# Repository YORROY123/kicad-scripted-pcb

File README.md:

# kicad-scripted-pcb

**[繁體中文](README.zh-TW.md)**

Three KiCad 10 boards designed entirely as code: Python scripts produce the schematic, the PCB
placement, the routing (via [freerouting](https://github.com/freerouting/freerouting)) and the
copper pours, and each board rebuilds from scratch with one command. The KiCad GUI is never opened.

The point is **verification**. Every build runs several independent checks, because each one is
blind to errors the others catch. Some of those errors turned up while these boards were being
built and are listed below.

| | Board | Result |
|---|---|---|
|  | **usbc-ldo**: USB-C 5 V → 3.3 V LDO → LED. 40 × 24 mm, 2 layers. Includes an ngspice power-path simulation. | ERC 0, DRC 0, schematic parity |
|  | **esp32c3**: ESP32-C3 minimal board with native USB, LP38693 LDO, RESET/BOOT, LEDs and an 8-pin header. 32 × 49 mm. | ERC 0, DRC 0, schematic parity, pin-by-pin netlist check |
|  | **relay8**: ESP32-C3 + ULN2803 driving 8 mains relays from **one mains cable**: on-board HLK-10M05 AC-DC (100–240 VAC), T8A fuse, varistor, L/N bus traces, per-channel NO · N · NC terminals, isolation slots and custom mains clearance rules. 232 × 110 mm. **Not safety-certified.** | ERC 0, DRC errors 0 (40 silkscreen-clipped-by-slot/edge warnings listed), schematic parity |

Each ESP32 board has a `FIRMWARE.md` with the pin map, flashing steps, a first program, and, for
relay8, the mains wiring.

## Pipeline

```
gen/board.py ──► .kicad_sch ──► ERC ──► netlist ──► netlist check (vs expected_nets.json)
                                                     │
                                                     ▼
                                     design review (lib/review.py, datasheet rules)
                                                     │
gen/pcb.py ◄─────────────────────────────────────────┘   place footprints, board outline,
   │                                                     net classes, placement self-check
   ▼
.kicad_pcb ──► Specctra DSN ──► freerouting ──► SES ──► import + GND pour ──► DRC (+ schematic parity)
                                                                                   │
                     lcsc.json ──► lib/lcsc.py (online, run by hand) ──► lcsc-check.json
                                                                                   │
                                                       lib/fab.py ◄────────────────┘
                                     Gerber + drill zip, JLCPCB BOM / CPL, hand-solder list
```

Every step stops the build on failure; nothing is passed downstream with a known error.

`kicad-cli` has no "update PCB from schematic" command, so `lib/pcbgen.py` builds the board from
the exported netlist with pcbnew.

## What each check catches, and what it missed

| Check | Catches | Missed here (caught by something else) |
|---|---|---|
| `schgen.crossing_pins()` / `overlapping_wires()` | a wire running across a pin (silent short), two nets merged by overlapping wires | — |
| KiCad ERC | unconnected pins, undriven power | **LED wired backwards** (two passive pins, ERC is fine with it). Found by reading the netlist while building the PCB. |
| `check_netlist.py` vs `expected_nets.json` | wrong pin→net, single-pin nets | ERC ignores "global label appears only once" **by default**, so a label typo creates an isolated net with no ERC error. Proven with a deliberate typo (mutation test). |
| placement self-check | pad nets vs netlist, footprints off-board, courtyard overlap | Uses real courtyard polygons. The ESP32 module's courtyard is T-shaped, and bounding boxes reject legal positions. |
| DRC + `--schematic-parity` | clearance, track width, edge clearance, schematic vs PCB | — |
| custom DRC rules (`relay8.kicad_dru`) | mains ↔ low voltage ≥ 3.0 mm, mains ↔ mains ≥ 2.4 mm | Creepage around the slots is not checked by DRC. Needs a human. |
| ngspice simulation (`usbc-ldo/sim`) | design margins | The first board's 1.1 V-dropout LDO falls out of regulation at USB's 4.40 V minimum, and its input capacitance injects ~124 µC on hot-plug (USB 2.0 limit: 50 µC). All three boards now use LP38693 (12 V input rating): `esp32c3/sim` showed that with only 1 µF on VBUS, hot-plug cable ringing reaches 7.7–8.6 V, above the 6.5 V rating of the AP2112K the ESP32 boards first used. |
| `lib/review.py` design review (datasheet rules on the netlist) | wrong *intent*: diode/TVS polarity, LED current from the real Vf range, decoupling and rail ranges per datasheet, USB-C CC pull-downs, ESP32-C3 EN RC / strapping pins / GPIO18-19, relay flyback path and pickup voltage, capacitor voltage and polarity, per-supply current budget, LDO junction temperature, USB VBUS capacitance | **usbc-ldo's SMAJ5.0A TVS was wired backwards**: anode on +5 V, cathode on GND, a short the moment USB is plugged in. KiCad's symbol names the cathode pin "A1". ERC, DRC, the netlist check and the SPICE model (which had it the right way round) all passed. It also found a blue LED on a 3.3 V GPIO (Vf up to 3.6 V) and green power LEDs at ~0.45 mA. `lib/review_test.py` breaks the real netlists 20 ways and expects each rule to fire. |
| `lib/lcsc.py` + `lib/fab.py` | LCSC part number vs model, stock, package size, R/C value, LED colour; symbol default footprint vs assigned footprint; drill count; BOM/CPL/board refdes | All three boards used the USBLC6-2**P6** symbol (SOT-666) on a SOT-23-6 footprint: same pinout, so nothing else noticed, but a BOM by value buys parts that do not fit. The SMAJ5.0A part number first chosen had zero stock. |

## Things that cost time (so they don't cost yours)

- **freerouting-cli 2.5.0 crashes** on KiCad 10 DSN files ([freerouting#957](https://github.com/freerouting/freerouting/issues/957)). Use the jar, which needs Java 25.
- freerouting's **automatic neck-down** narrows tracks to 0.125 mm beside 0402 pads, below JLCPCB's 0.127 mm minimum. Use `--router.automatic_neckdown=false --router.neck_width_um=150`.
- The DSN carries no copper-to-edge rule. Pass `--router.copper_to_edge_clearance_um`. That setting **does not cover internal slots**, so put keepouts around slots.
- Net classes live in `.kicad_pro`, not `.kicad_pcb`. Save with `pcbnew.SaveBoard()`, which writes both.
- `board.Remove(zone)` from Python can raise `'SwigPyObject' has no attribute 'thisown'` or crash pcbnew (0xC0000005). Use `board.Delete()`.
- freerouting reports pin-to-pin "violations" inside fine-pitch footprints where KiCad's DRC is clean. The cause is KiCad's DSN exporter inflating **every** edge of a rounded-rect pad (`specctra_export.cpp`) by the arc-approximation margin.
- Windows PowerShell 5.1 reads BOM-less UTF-8 scripts as ANSI. The build scripts here are ASCII-only for that reason.

## Requirements

- Windows (the build scripts are PowerShell; the Python parts are cross-platform)
- [KiCad 10](https://www.kicad.org/) (uses its bundled Python for pcbnew, and its ngspice). Set `KICAD_BIN` / `KICAD_SHARE` if it is not in the default location.
- Python 3.10+ on PATH for schematic generation and the design review (standard library only). The simulations and the field solver need `numpy`, `scipy` and `matplotlib`.
- Network access only for `lib/lcsc.py` (JLCPCB parts API). The build itself runs offline.
- freerouting 2.5.0 jar + a Java 25 runtime. Run `tools\setup-tools.ps1` once; it downloads both into `tools\` with pinned SHA-256 checks.

## Quick start

```powershell
powershell -ExecutionPolicy Bypass -File tools\setup-tools.ps1
powershell -ExecutionPolicy Bypass -File boards\esp32c3\build.ps1
python lib\review_test.py          # design-review mutation tests; needs the boards built once
```

The build ends with `boards/<b>/fab/`:

| File | Use |
|---|---|
| `<b>-gerber.zip` | upload to JLCPCB as the PCB |
| `<b>-bom.csv`, `<b>-cpl.csv` | upload for SMT assembly (parts LCSC can supply) |
| `hand-solder.csv` | parts LCSC cannot supply (relay8: mains terminals, fuse holders) |
| `rotation-review.csv` | every part's CPL rotation and where it came from. None is hardware-verified: compare each part in JLCPCB's placement preview |

Also written to `boards/<b>/`: `review.txt` (design review, including the inferred net voltages) and
`lcsc-check.json` (part numbers as checked against JLCPCB, with stock and attributes).

## Layout

```
lib/schgen.py, ksym.py, netlabel.py   schematic writer (symbols flattened from the KiCad library)
lib/check_netlist.py                  netlist vs expected_nets.json
lib/review.py, review_test.py         design review rules + mutation tests
lib/pcbgen.py, route.py               PCB builder (BoardSpec), freerouting round trip, GND pour
lib/lcsc.py, fab.py, jlc_rotations.json   part-number check, fabrication outputs
lib/field2d.py, field2d_check.py      2-D field solver for trace impedance + validation
boards/<b>/gen/board.py   the circuit (pin -> net table)
boards/<b>/gen/pcb.py     placement (BoardSpec)
boards/<b>/lcsc.json      hand-written LCSC part numbers ("value|footprint" -> part)
boards/<b>/review-waivers.json   accepted review findings, each with a reason
boards/<b>/build.ps1      one-command build
boards/<b>/sim/           ngspice and field-solver studies
tools/      setup-tools.ps1 (downloads are git-ignored)
```

Want to add a board or a review rule? See [CONTRIBUTING.md](CONTRIBUTING.md).

Code comments are in Chinese. The boards were built while comparing AI-assisted workflows in
KiCad and EasyEDA Pro.

## Limits

These are two-layer boards with modules and simple power. There is no controlled-impedance routing,
no length matching, no BGA and no SI/PI analysis; freerouting does none of these (`lib/field2d.py`
can tell you whether a trace needs it). The fabrication files are complete enough to order, but
nobody has built these boards yet: CPL rotations are unverified and the design review is a set of
rules, not an engineer. Have a person review before ordering. This applies above all to
**relay8**, which switches mains voltage.

## License

MIT. freerouting (GPL-3.0) and the Temurin JRE (GPL-2.0 with Classpath Exception) are downloaded at
setup time and are not part of this repository.

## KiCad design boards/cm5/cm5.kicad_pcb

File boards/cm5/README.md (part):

# CM5 carrier(進行中)

Raspberry Pi Compute Module 5(含 eMMC)的通用載板,目標是 JLCPCB 能直接 PCBA,CM5 自己插上。

原理圖已完成。PCB 進行中:擺件完成,佈線第一、二階段(兩級降壓的鋪銅與過孔、閘極驅動)完成,第三階段(差分線)全部手佈完成,其餘還沒佈線(交給 freerouting)。3D 預覽在 [`concept/`](concept/README.md)。

## PCB(進行中)

`gen/pcb.py` 讀網表擺出 `cm5.kicad_pcb`;座標與自動擺件在 `gen/placement.py`,3D 預覽也用同一份。
電源級的外層鋪銅、過孔與手佈走線在 `gen/power_stage.py`(見「電源級」「閘極驅動」兩節)。
差分線在 `gen/diff_pairs.py`(見「差分線」)。

- 170 × 120 mm、4 層。固定孔:板子 M3 ×4(H1–H4),CM5 模組 M2.5 ×4(H5–H8)。
- 網路類別(線寬由電流算,見下一節「外層電源走線」):`HV54`(+54V、VIN_RAW;1.4 mm、間距 0.25 mm)、
  `PoE`(POE*;0.5 mm、0.25 mm)、`Switch`(SW、SW3;主路徑是鋪銅)、`Rail5`(+5V;2.7 mm)、`Rail3`(+3V3;1.1 mm)、
  `USB5V`(USB-A / HDMI / USB-C 的 VBUS;0.75 mm)、`Power`(GND 與其他小電源;0.5 mm)。
  54 V 間距取 IPC-2221 表 6-1 的 B4(外層有防焊,51–100 V 0.13 mm)再留餘量;B2(無塗層)的 0.6 mm
  零件本身做不到(RJ45 腳間 0.53、IP804AR 0.25)。
- `cm5.kicad_dru`:同一顆零件的焊盤之間最小 0.1 mm(FSUSB42 MSOP-10 焊盤間只有 0.15 mm),
  走線與過孔仍照網路類別。拿掉這個檔,DRC 會報 FSUSB42 的 8 個間距錯誤。
- 自檢(`lib/pcbgen.py`):焊盤逐腳對網表、courtyard 真實多邊形不重疊、不出板(板邊接頭只查焊盤)。
  `build.ps1` 與 CI 再跑 DRC + 原理圖一致性,除了未連接以外不能有錯誤。
- SW51(FLASH/RUN 滑動開關):撥桿在封裝局部 +y,所以 0°;固定腳到 y=1.83,銅到板邊要 ≥0.5 mm,
  本體退到板邊內 0.75 mm,撥桿伸出約 0.8 mm。外殼開孔時要確認撥得到。

### 差分阻抗(`sim/diff_impedance.py`,結果 `sim/diff_impedance.txt`)

目標照 CM5 規格書 §2.2–2.5:PCIe、USB 3.0、USB 2.0 都是 **90 Ω**,HDMI 與乙太網路 **100 Ω**
(先前這裡寫 PCIe 85 Ω 是錯的)。疊構 JLC04161H-3313(jlcpcb.com/impedance):L1 銅 0.035 mm、
3313 預浸料 0.0994 mm、εr 4.1,差分線走 L1、參考 L2 整片地(L4 對 L3 疊構相同,但 L3 是電源平面,只用來短暫下穿)。`lib/field2d.py` 外推到格距 → 0:

| 用途 | 目標 | 線寬 | 間距 | 算出 |
|---|---|---|---|---|
| PCIe / USB3 / USB2 | 90 Ω | 0.165 mm | 0.15 mm | 90.5 Ω |
| 同上(較緊) | 90 Ω | 0.155 mm | 0.13 mm | 91.0 Ω |
| HDMI / Ethernet | 100 Ω | 0.145 mm | 0.20 mm | 100.2 Ω |
| 同上(較緊) | 100 Ω | 0.130 mm | 0.15 mm | 101.0 Ω |

- 同層鋪銅離差分線 ≥ 0.25 mm 時,阻抗只低 0.4%;0.15 mm 會低 1.5%。
- 防焊漆沒建模(實際再低約 1–3 Ω),所以結果故意落在目標上方。下單前要用 JLC 自己的計算器
  (有建模防焊與梯形線)對一次,並選阻抗控制。
- 換層:L1 ↔ L4 的參考面從 L2(地)換成 L3(電源),旁邊放地過孔接不到 L3,沒有用;要的是 GND–電源的
  縫合電容(見「差分線」待辦)。L4 段不能跨 L3 的 +5V / +3V3 分界。

### 外層電源走線(`gen/pcb.py` 的 `CURRENTS`)

IPC-2221 §6.2 外層公式,外層 1 oz(0.035 mm)、溫升 10 °C。電流取「保護動作前能一直流的電流」:
限流開關用限流**上限**,不是額定。網路類別的線寬比算出的窄,`gen/pcb.py` 就刪掉板檔、回傳失敗。

| 網 | 電流 | 依據 | 需要 | 類別線寬 |
|---|---|---|---|---|
| VIN_RAW、+54V | 3.0 A | 120 W ÷ UVLO 40 V | 1.37 mm | 1.4 mm |
| POE0/1_P、_N | 0.92 A | IP804AR 限流上限(保險絲 1.5 A 只在故障時斷) | 0.27 mm | 0.5 mm |

+5V(→ U62/U63/U70、CM5)與 +3V3(→ M.2)的外層大電流路徑改由「外層供電支線」的鋪銅檢查,
類別線寬降回焊盤放得下的寬度(+5V 0.4、+3V3 0.25),見下一節。
| USBA0/1_VBUS | 1.9 A | AP2171W 限流上限 | 0.73 mm | 0.75 mm |
| HDMI_5V | 1.05 A | TPS2051C 限流上限 | 0.32 mm | 0.75 mm |

- 開關節點與降壓器輸出到內層平面的過孔見下一節「電源級」。
- ⚠ +5V 預算:LM5146 設計 12 A。額定負載 CM5 5 A + 40-pin 1 A + 風扇 0.5 A + USB-A 2 × 1 A + HDMI 0.5 A
  + TPS568230 輸入約 3.0 A(3.3 V × 4 A ÷ 90% ÷ 4.87 V)≈ 12.0 A,剛好到頂。所有限流開關都頂到上限時
  約 14.4 A,會先碰到 LM5146 的限流。要不要降 USB-A 的限流檔或改 12 A 以上的降壓器,佈線前決定。
- `gen/board.py` 的 TPS2051C 註解原本寫限流 0.5–0.9 A,規格書 §6.7(−40–125 °C)是 0.65–1.05 A,已改。

### 外層供電支線(`gen/feeds.py`)與平面扇出(`lib/fanout.py`)

網路類別的線寬整條網共用。+5V 原本 2.7 mm、+3V3 1.1 mm 是照最大的支路算的,結果 LAN7800 / USB2514B
0.25 mm 寬、0.5 mm 腳距的 QFN 腳也要接 1.1 mm 的線,freerouting 扇不出去。現在大電流路徑用固定鋪銅畫死:

| 支線 | 電流 | 做法 | 過孔(每個 0.71 A) |
|---|---|---|---|
| In2 +5V → U62、U63、U70 | 4.85 A | 開關擺在 In2 的 +3V3 區:CM5 模組底邊過孔陣列 → B.Cu 主幹 x 89.5–93.6(避開 USBA0 下穿)→ y 91.3–95.6 橫向 → 每顆 5 腳旁一小塊 F.Cu | 12 / 3 / 3 / 2 |
| In2 +5V → CM5 J1 77–87 | 5 A | 腳下方 F.Cu + 5×2 過孔 | 10 |
| In2 +3V3 → M.2 3V3 腳 | 2.5 A | 右排三組腳外側(卡底下)各一塊 F.Cu | 2 / 3 / 2 |

自檢:載流截面(B.Cu 主幹 3.70 mm ≥ 2.65)、過孔數、F.Cu 小鋪銅的過孔也要落在 B.Cu 主幹上、
每支目標腳最後都接到同網的 In2 平面。突變:U62 過孔 3 → 2、M.2 2/4 腳的鋪銅右移離開焊盤,都會失敗。

平面網路(GND → In1、+3V3 / +5V → In2)的 SMD 焊盤由 `lib/fanout.py` 先打好過孔 + 短線(鎖定):
過孔要落在該網平面的銅上、與異網銅保持兩邊類別較大的間距、孔距 0.25、不進其他零件 courtyard;
短線不比焊盤窄邊寬(CM5 連接器 0.2 mm 焊盤用 0.25 的線離隔壁腳只剩 0.175)。QFN 散熱焊盤
(U40、U41、U50、U61)焊盤內 3×3 過孔。目前 302 個過孔,找不到位置 9 個(C210 / C213 / C230 那裡
In2 是 +3V3 區,沒有 +5V 平面可接,由佈線接到供電支線)。DRC 0。

### 內層電源平面(`gen/pcb.py` 的 `PLANES` / `CORRIDORS`)

- L2(In1.Cu)整片 GND,當 L1 差分線的參考面。
- L3(In2.Cu)分兩塊、中間留 0.5 mm:**+5V** 在右上(x ≥ 60、y ≤ 72),L10 降壓輸出 → CM5、40-pin、風扇;
  **+3V3** 是 L 形(下緣 y ≥ 72 + 左緣 x ≤ 60),L20 降壓輸出 → Hub、LAN7800 ×2 → 往上到 M.2。
- 自檢:每條載流走廊要整塊落在該網的平面裡,而且寬度 ≥ IPC-2221 §6.2 內層公式算出的寬度
  (JLC 內層銅 0.0152 mm、溫升 10 °C;對平面很保守)。不過就刪掉板檔、回傳失敗。

| 網 | 電流 | 走廊寬 | IPC-2221 需要 |
|---|---|---|---|
| +5V(L10 → CM5、40-pin、風扇) | 6.5 A | 71.5 mm | 23.8 mm |
| +3V3(L20 → Hub、LAN7800) | 4.0 A | 47.5 mm | 12.2 mm |
| +3V3(左緣 → M.2) | 2.5 A | 59.5 mm | 6.4 mm |

電流:CM5 5 V 最多 5 A(規格書 §1);M.2 3.3 V 2.5 A(M.2 規範上限);LAN7800 ×2 0.592 A;
40-pin 1 A、風扇 0.5 A、其他 3.3 V 0.3 A 是估計。注意 IPC-2221 這個寬度是 0.5 oz 內層的值:
若整顆降壓器 12 A 都走平面,需要約 55 mm,現在的佈局給得起,但 USB/HDMI 的 5 V 不走平面。
突變:+5V 平面下緣縮到 y = 50 → 走廊落在平面外;+5V 電流改 30 A → 寬度不足,兩者都會失敗。
平面只刪小於 3 mm² 的孤島(`PLANE_MIN_ISLAND_MM2`):40-pin 排針腳之間約 2.2 mm² 的碎銅、過孔陣列之間
< 0.5 mm² 的碎銅都沒接任何東西,以前留著,DRC 報 22 個 isolated_copper 警告;現在 0 個。
還沒接到焊盤的整塊平面不刪。

### 電源級(佈線第一階段;`gen/power_stage.py`)

功率件改成手擺(`gen/placement.py` 的 `PLACE`),照 LM5146 規格書 SNVSBV0A §11.1 與 TPS568230 SLVSEY5C §10.1
(兩份都在 TI 官網);小件仍自動擺,但避開鋪銅與過孔(`power_stage.keepouts()`)。

- **LM5146 → +5V**:Q10 轉 180、Q11 不轉,上下疊。開關節點(Q10 源極、Q11 汲極 → L10)在右側一直線;
  熱迴路(輸入電容 → Q10 汲極 … Q11 源極 → 電容)在左側,C11/C13/C16 的 + 端貼 Q10 汲極、− 端貼 Q11 源極,
  地過孔靠 Q11 源極(§11.1.5)。U10 轉 270,閘極驅動腳朝下正對 Q10;VCC、自舉電容(C20、C21)在 U10 與 Q10 之間。
  54 V 輸入 J20 移到右上,F1 → C10 → 一條 2.1 mm 的 +54V 鋪銅帶往下接輸入電容。
- **TPS568230 → +3V3**:U20 轉 180,VIN 朝右接 C45、SW(19/20 腳)朝下接 L20。整級跨在 In2 分界上:
  輸入取 +5V 平面(5 個過孔),L20 的 2 腳在 +3V3 平面上(8 個過孔)。
- 13 塊 F.Cu 鋪銅都有名字、優先序 1(蓋過之後的整面 GND);80 個過孔鎖定。`lib/route.py` 重新匯入佈線時
  留下它們(`lib/route_test.py`),匯出的 DSN 裡鋪銅是 `plane`、過孔是 `(type fix)`,freerouting 不會動。
- 自檢(`gen/pcb.py` 的 `add_power_stage`,不過就刪掉板檔):每塊鋪銅填得出來、每個過孔在自己網的銅上、
  載流截面整塊有銅、過孔數夠:

| 截面 / 過孔 | 電流 | 寬 | IPC-2221 外層 | 判斷 |
|---|---|---|---|---|
| +54V 帶子(F1 / C10 → 輸入電容) | 3.0 A | 1.7 mm | 1.37 mm | 寬度夠 |
| SW:Q11 汲極 → L10(長 2.35 mm) | 12 A | 4.5 mm | 9.25 mm | 短頸,I²R 37 mW |
| SW3:U20 腳 → L20(長 0.9 mm) | 8 A | 0.85 mm | 5.29 mm | 短頸,I²R 33 mW;受限於 IC 腳寬 |
| +5V:L10 2 腳 → 第一排過孔(長 0.45 mm) | 12 A | 6.3 mm | 9.25 mm | 短頸,I²R 5 mW |
| +3V3:L20 2 腳 → 過孔與輸出電容(長 3.6 mm) | 4.0 A | 2.9 mm | 2.03 mm | 寬度夠 |
| 過孔 L10 → In2 +5V | 12 A | 27 個 | 至少 17 | |
| 過孔 In2 +5V → U20 | 3.0 A | 5 個 | 至少 5 | |
| 過孔 L20 → In2 +3V3 | 4.0 A | 8 個 | 至少 6 | |

  IPC-2221 的寬度是長走線的溫升;開關節點 TI 要求面積越小越好(§11.1.4,它是 EMI 來源),所以 ≤ 3 mm 的
  短頸改算 I²R(銅 1.72e-5 Ω·mm),上限 0.1 W(MOSFET 本身約 1 W 量級)。截面取兩端焊盤之間整段窄處,
  長度照實(只切一薄片的話,任何電流都會被當成短頸放過)。
  突變:拿掉 12 個 +5V 過孔、SW 鋪銅縮窄、過孔移出銅、+3V3 電流改 9 A,四種都會失敗。
- 過孔數改了:以前寫 L10 → +5V 平面 6.5 A、10 個,只算了 CM5、40-pin、風扇;USB-A / HDMI 開關和 U20 的輸入
  也從 +5V 平面取電,LM5146 設計的 12 A 全部要經過這些過孔 → 至少 17 個。
- 還沒做:U10、U20 散熱焊盤下的地過孔(TI §11.1.4):過孔打在焊盤裡要選 JLC 的樹脂塞孔,下單前決定。

### 閘極驅動(佈線第二階段;`gen/power_stage.py` 的 `TRACKS`)

手佈、鎖定的 28 段走線與 4 個過孔(DSN 裡都是 `(type fix)`)。U10 底排腳距 0.5 mm,由左到右
12 GND、13 LO、14 VCC、15 GND、16 NC、17 BST、18 HO、19 SW;腳間出線只能 0.24–0.25 mm,離開腳位才加寬。

- **C21(自舉)不跨 HO**:第一階段以為一定要過孔。改成直放在 16 腳(NC)下:上端直連 17 腳 BST,
  下端一條 0.4 mm 線從 Q10 汲極與閘極焊盤之間直下 SW 鋪銅。HO(18 腳)0.65 mm 直下 Q10 閘極,
  19 腳 SW 在它右側並行回 Q10 源極,即 TI §11.1.2 的「HO 與 SW 成對走」。
- **C20(VCC)轉 180°**:GND 端在 12 腳下、VCC 端在 14 腳下,都是直線;兩焊盤之間 0.65 mm 剛好讓 LO 出去。
- **LO**:過孔換到 B.Cu,0.65 mm 直線到 Q11 閘極,約 12 mm,是唯一換層的閘極線。Q11 的源極要朝左接熱迴路,
  閘極腳就只能在左下角。B.Cu 下面的參考面是 In2 +5V(交流上等同地)。
- **U20 6 腳**(SW3 的另一支,上方是 C47、右邊是 +5V 輸入):C47 往上挪 0.6 mm,6 腳打過孔走 B.Cu 回 SW3 鋪銅。
  B.Cu 走 +5V 腳下方,不經 EP 正下方,留給散熱過孔。
- 也手佈了 C47 → 8 腳 GND 與 +5V 鋪銅、BST3(1 腳 → C49,穿過 SW3 鋪銅的缺口)。VCC3(C48)交給 freerouting。
- 自檢:HO、LO、BST、VCC、SW3、BST3 每條網的焊盤都要接通(`GetConnectedItems`)。
  突變:HO 截短到閘極前、刪掉 6 腳那段,都會失敗。DRC 0 錯誤;未接數(pcbnew 實算)695 → 684。
  `kicad-cli` 報告的「499 unconnected」是它的上限,不是實際數字。

### 差分線(佈線第三階段;`gen/diff_pairs.py`)

每對寫一條中心線,程式切 45° 角、往兩側偏移出 P、N(線寬 / 間距照「差分阻抗」),兩端自動接到 P、N 網的
焊盤;換層處放一對過孔(中心距 1 mm)。走線與過孔都鎖定。對內間距 0.15 mm 比網路類別的 0.2 mm 小,
`cm5.kicad_dru` 每對加一條規則(下限 0.14,留給座標捨入)。

| 對 | 長 | 換層 | 說明 |
|---|---|---|---|
| PCIe REFCLK | 127 mm | 0 | J2 頂排往北 → 向西 → 從 M.2 插座南端繞到腳後 |
| PCIe TX | 128 mm | 0 | 同上 |
| PCIe RX | 122 mm | 1 | 在 x ≈ 45 從 TX 底下穿過(B.Cu 約 4 mm,L3 為 +3V3) |
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
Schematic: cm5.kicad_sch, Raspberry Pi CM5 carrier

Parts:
BT50: CR2032; BatteryHolder_Keystone_3034_1x20mm
C10: 100uF; CP_Radial_D12.5mm_P5.00mm
C11, C12, C13, C14, C15, C16: 4.7uF; C_1210_3225Metric
C17: 100nF; C_0603_1608Metric
C18: 47nF; C_0402_1005Metric
C19: 15pF; C_0402_1005Metric
C20: 2.2uF; C_0603_1608Metric
C21, C47, C49, C51, C60, C70, C71, C72, C73, C74, C75, C76, C77, C88, C101, C102, C103, C104, C106, C107, C108, C109, C111, C112, C113, C114, C115, C120, C121, C131, C132, C133, C134, C136, C137, C138, C139, C141, C142, C143, C144, C145, C150, C151, C200, C202, C203, C204, C205, C206, C207, C212, C215, C222, C230, C231, C240, C241, C242, C243, C244, C245, C246, C247, C248, C249, C250, C251, C252, C253: 100nF; C_0402_1005Metric
C22: 6.8nF; C_0402_1005Metric
C23: 150pF; C_0402_1005Metric
C24: 820pF; C_0402_1005Metric
C30, C31, C32, C33, C34, C40, C41, C42, C43, C45, C46, C50, C220, C221: 47uF; C_1210_3225Metric
C44: 100pF; C_0402_1005Metric
C48, C105, C117, C135, C147, C210, C213: 1uF; C_0402_1005Metric
C82: 1uF; C_1206_3216Metric
C83: 47uF; CP_Elec_10x10
C84, C85, C86, C87, C201: 4.7uF; C_0603_1608Metric
C90, C91: 1nF 2kV; C_1206_3216Metric
C92, C93: 100nF; C_0805_2012Metric
C100, C110, C130, C140: 10uF; C_0805_2012Metric
C118, C119, C148, C149: 27pF; C_0402_1005Metric
C208, C209: 22pF; C_0402_1005Metric
C211, C214: 100uF; CP_Elec_6.3x7.7
D20, D60, D61: SM6T68A; D_SMB
D40, D42, D51: GREEN; LED_0805_2012Metric
D41, D43: YELLOW; LED_0805_2012Metric
D50: RED; LED_0805_2012Metric
D70, D71, D72: USBLC6-2SC6; SOT-23-6
F1: 4A 63V; Fuse_1206_3216Metric
F40, F41: 1.5A; Fuse_1206_3216Metric
J1: CM5 pins 1-100; Amphenol_10164227-1001A1RLF_2x50_P0.4mm
J2: CM5 pins 101-200; Amphenol_10164227-1001A1RLF_2x50_P0.4mm
J20: 54V IN; TerminalBlock_Phoenix_MKDS-1,5-2-5.08_1x02_P5.08mm_Horizont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
J30: HR911130A; RJ45_Hanrun_HR911130A_Horizontal
J40: POE0; RJ45_Amphenol_RJHSE5380
J41: POE1; RJ45_Amphenol_RJHSE5380
J50: USB-C FLASH; USB_C_Receptacle_HRO_TYPE-C-31-M-12
J51: USB-A 1; USB_A_Molex_48037-2200_Horizontal
J52: USB-A 2; USB_A_Molex_48037-2200_Horizontal
J60: M.2 M-key; M.2_Socket_M_TE_1-2199230-6
J70: HDMI; HDMI_A_Molex_208658-1001_Horizontal
J80: GPIO 40-pin; PinHeader_2x20_P2.54mm_Vertical
J81: FAN; JST_SH_SM04B-SRSS-TB_1x04-1MP_P1.00mm_Horizontal
L10: 3.3uH SPM10065VT; L_Bourns_SRP1050WA
L20: 1.5uH IHLP4040; L_Vishay_IHLP-4040
L40, L41: 3.3uH; L_1008_2520Metric
Q10: BSC160N10NS3G; TDSON-8-1
Q11: BSC070N10NS5; TDSON-8-1
R10: 402k; R_0805_2012Metric
R11: 12.4k; R_0402_1005Metric
R12: 33.2k; R_0402_1005Metric
R13: 412; R_0805_2012Metric
R14: 23.2k; R_0402_1005Metric
R15: 4.42k; R_0402_1005Metric
R16: 7.5k; R_0402_1005Metric
R17: 150; R_0402_1005Metric
R18, R74, R75, R76, R77, R78, R102, R132, R205, R206, R207, R208, R209, R230: 10k; R_0402_1005Metric
R21: 91k; R_0402_1005Metric
R22: 20k; R_0402_1005Metric
R23: 330k; R_0402_1005Metric
R24, R200, R201: 5.1k; R_0402_1005Metric
R25, R202, R203, R204: 100k; R_0402_1005Metric
R50, R51: 1k; R_0402_1005Metric
R60, R61, R104, R105, R134, R135: 470; R_0402_1005Metric
R80, R81, R82, R83: 75; R_0603_1608Metric
R100, R130: 2k; R_0402_1005Metric
R101, R131, R210: 12k; R_0402_1005Metric
R211: 1M; R_0402_1005Metric
SW50: POWER; SW_Push_1P1T_NO_CK_KMR2
SW51: FLASH/RUN; SW_SPDT_PCM12
T40, T41: G2423S; Transformer_CNDtek_G2423S
U10: LM5146RGYR; Texas_RGY_R-PVQFN-N20_EP2.05x3.05mm
U20: TPS568230RJER; Texas_RJE0020A_VQFN-20-1EP_3x3mm_P0.45mm_EP0.675x0.76mm
U30, U31: TPD4EUSB30; USON-10_2.5x1.0mm_P0.5mm
U40, U41: LAN7800/Y9X; QFN-48-1EP_7x7mm_P0.5mm_EP5.3x5.3mm
U50: IP804AR; QFN-48-1EP_7x7mm_P0.5mm_EP5.3x5.3mm
U60: FSUSB42MUX; MSOP-10_3x3mm_P0.5mm
U61: USB2514B; QFN-36-1EP_6x6mm_P0.5mm_EP3.7x3.7mm
U62, U63: AP2171W; SOT-23-5
U70: TPS2051CDBV; SOT-23-5
Y40, Y41: 25MHz; Crystal_SMD_3225-4Pin_3.2x2.5mm
Y60: 24MHz; Crystal_SMD_2520-4Pin_2.5x2.0mm

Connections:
+3V3: C40.1, C41.1, C42.1, C43.1, C44.1, C100.1, C101.1, C102.1, C103.1, C104.1, C130.1, C131.1, C132.1, C133.1, C134.1, C201.1, C202.1, C203.1, C204.1, C205.1, C220.1, C221.1, C222.1, C240.1, C246.1, C247.1, C248.1, C249.1, C250.1, C251.1, C252.1, C253.1, D40.2 (A), D41.2 (A), D42.2 (A), D43.2 (A), J60.2 (3.3V), J60.4 (3.3V), J60.12 (3.3V), J60.14 (3.3V), J60.16 (3.3V), J60.18 (3.3V), J60.70 (3.3V), J60.72 (3.3V), J60.74 (3.3V), L20.2, R21.1, R25.1, R205.1, R206.1, R207.1, R208.1, R209.1, U40.14 (VDD_SW_IN), U40.20 (VDDVARIO), U40.23 (VBUS_DET), U40.36 (VDDVARIO), U40.38 (VDD33A), U40.39 (VDDVARIO), U40.46 (VDD33_REG_IN), U41.14 (VDD_SW_IN), U41.20 (VDDVARIO), U41.23 (VBUS_DET), U41.36 (VDDVARIO), U41.38 (VDD33A), U41.39 (VDDVARIO), U41.46 (VDD33_REG_IN), U61.5 (VDDA33), U61.10 (VDDA33), U61.15 (VDD33), U61.23 (VDD33), U61.27 (VBUS_DET), U61.29 (VDDA33), U61.36 (VDDA33)
+5V: C30.1, C31.1, C32.1, C33.1, C34.1, C45.1, C46.1, C47.1, C50.1, C51.1, C210.1, C213.1, C230.1, C241.1, C242.1, C243.1, C244.1, C245.1, J1.77 (5V), J1.79 (5V), J1.81 (5V), J1.83 (5V), J1.85 (5V), J1.87 (5V), J80.2, J80.4, J81.1, L10.2, R14.1, R17.1, U20.2 (VIN), U20.3 (VIN), U20.4 (VIN), U20.5 (VIN), U62.5 (IN), U63.5 (IN), U70.5 (IN)
+54V: C10.1, C11.1, C12.1, C13.1, C14.1, C15.1, C16.1, C17.1, C82.1, C83.1, D20.1 (A1), F1.2, F40.1, F41.1, Q10.5 (D), R10.1, U10.20 (VIN), U50.17 (V54)
BST: C21.1, U10.17 (BST)
BST3: C49.1, U20.1 (BST)
CM5U0_RX_N: C120.2, J2.28 (USB3-0-RX_N)
CM5U0_RX_P: C121.2, J2.30 (USB3-0-RX_P)
CM5U1_RX_N: C151.2, J2.57 (USB3-1-RX_N)
CM5U1_RX_P: C150.2, J2.59 (USB3-1-RX_P)
CM5_1V8: J1.88 (CM5_1.8V), J1.90 (CM5_1.8V)
CM5_3V3: C200.1, D50.2 (A), D51.2 (A), J1.78 (GPIO_VREF), J1.84 (CM5_3.3V), J1.86 (CM5_3.3V), J30.11 (LEDG_A), J30.14 (LEDY_A), J80.1, J80.17, R18.1, R230.1, U60.1 (VCC), U70.4 (EN)
CM5_USB_N: J2.3 (USB_N), U60.4 (D-)
CM5_USB_P: J2.5 (USB_P), U60.3 (D+)
COMP: C23.1, R16.1, U10.4 (COMP)
COMP_RC: C22.1, R16.2
EN_UVLO: R10.2, R11.1, U10.1 (EN/UVLO)
ETH0_N: J1.10 (Ethernet_Pair0_N), J30.3 (MDI0-), U30.4 (D2+), U30.7 (NC)
ETH0_P: J1.12 (Ethernet_Pair0_P), J30.2 (MDI0+), U30.5 (D2-), U30.6 (NC)
ETH1_N: J1.6 (Ethernet_Pair1_N), J30.4 (MDI1+), U30.2 (D1-), U30.9 (NC)
ETH1_P: J1.4 (Ethernet_Pair1_P), J30.7 (MDI1-), U30.1 (D1+), U30.10 (NC)
ETH2_N: J1.9 (Ethernet_Pair2_N), J30.5 (MDI2+), U31.4 (D2+), U31.7 (NC)
ETH2_P: J1.11 (Ethernet_Pair2_P), J30.6 (MDI2-), U31.5 (D2-), U31.6 (NC)
ETH3_N: J1.5 (Ethernet_Pair3_N), J30.9 (MDI3-), U31.2 (D1-), U31.9 (NC)
ETH3_P: J1.3 (Ethernet_Pair3_P), J30.8 (MDI3+), U31.1 (D1+), U31.10 (NC)
ETH_CT: C60.1, J30.1 (CT)
ETH_LEDG_K: J30.12 (LEDG_K), R60.1
ETH_LEDY_K: J30.13 (LEDY_K), R61.1
ETH_nACT: J1.15 (Ethernet_nLED3), R60.2
ETH_nSPD: J1.17 (Ethernet_nLED2), R61.2
FAN_PWM: J1.19 (Fan_PWM), J81.2, R230.2
FAN_TACHO: J1.16 (Fan_Tacho), J81.4
FB: C22.2, C23.2, C24.2, R14.2, R15.1, U10.5 (FB)
FB3: C44.2, R21.2, R22.1, U20.14 (FB)
FB_FF: C24.1, R17.2
GND: BT50.2 (-), C10.2, C11.2, C12.2, C13.2, C14.2, C15.2, C16.2, C17.2, C18.2, C19.2, C20.2, C30.2, C31.2, C32.2, C33.2, C34.2, C40.2, C41.2, C42.2, C43.2, C45.2, C46.2, C47.2, C48.2, C50.2, C51.2, C60.2, C70.2, C71.2, C72.2, C73.2, C74.2, C75.2, C76.2, C77.2, C82.2, C83.2, C84.2, C85.2, C86.2, C87.2, C88.2, C90.2, C91.2, C100.2, C101.2, C102.2, C103.2, C104.2, C105.2, C106.2, C107.2, C108.2, C109.2, C110.2, C111.2, C112.2, C113.2, C114.2, C115.2, C117.2, C118.2, C119.2, C130.2, C131.2, C132.2, C133.2, C134.2, C135.2, C136.2, C137.2, C138.2, C139.2, C140.2, C141.2, C142.2, C143.2, C144.2, C145.2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
GPIO2: J1.58 (GPIO2), J80.3
GPIO3: J1.56 (GPIO3), J80.5
GPIO4: J1.54 (GPIO4), J80.7
GPIO5: J1.34 (GPIO5), J80.29
GPIO6: J1.30 (GPIO6), J80.31
GPIO7: J1.37 (GPIO7), J80.26
GPIO8: J1.39 (GPIO8), J80.24
GPIO9: J1.40 (GPIO9), J80.21
GPIO10: J1.44 (GPIO10), J80.19
GPIO11: J1.38 (GPIO11), J80.23
GPIO12: J1.31 (GPIO12), J80.32
GPIO13: J1.28 (GPIO13), J80.33
GPIO14: J1.55 (GPIO14), J80.8
GPIO15: J1.51 (GPIO15), J80.10
GPIO16: J1.29 (GPIO16), J80.36
GPIO17: J1.50 (GPIO17), J80.11
GPIO18: J1.49 (GPIO18), J80.12
GPIO19: J1.26 (GPIO19), J80.35
GPIO20: J1.27 (GPIO20), J80.38
GPIO21: J1.25 (GPIO21), J80.40
GPIO22: J1.46 (GPIO22), J80.15
GPIO23: J1.47 (GPIO23), J80.16
GPIO24: J1.45 (GPIO24), J80.18
GPIO25: J1.41 (GPIO25), J80.22
GPIO26: J1.24 (GPIO26), J80.37
GPIO27: J1.48 (GPIO27), J80.13
HDMI0_CEC: J2.51 (HDMI0_CEC), J70.13 (CEC)
HDMI0_CK_N: J2.90 (HDMI0_CLK_N), J70.12 (CK-)
HDMI0_CK_P: J2.88 (HDMI0_CLK_P), J70.10 (CK+)
HDMI0_D0_N: J2.84 (HDMI0_TX0_N), J70.9 (D0-)
HDMI0_D0_P: J2.82 (HDMI0_TX0_P), J70.7 (D0+)
HDMI0_D1_N: J2.78 (HDMI0_TX1_N), J70.6 (D1-)
HDMI0_D1_P: J2.76 (HDMI0_TX1_P), J70.4 (D1+)
HDMI0_D2_N: J2.72 (HDMI0_TX2_N), J70.3 (D2-)
HDMI0_D2_P: J2.70 (HDMI0_TX2_P), J70.1 (D2+)
HDMI0_HPD: J2.53 (HDMI0_HOTPLUG), J70.19 (HPD)
HDMI0_SCL: J2.100 (HDMI0_SCL), J70.15 (SCL)
HDMI0_SDA: J2.99 (HDMI0_SDA), J70.16 (SDA)
HDMI_5V: C231.1, J70.18 (+5V), U70.1 (OUT)
HO: Q10.4 (G), U10.18 (HO)
HUB_CFG0: R202.1, U61.24 (SCL/SMBCLK/CFG_SEL0)
HUB_CFG1: R203.1, U61.25 (HS_IND/CFG_SEL1)
HUB_CRFILT: C206.1, U61.14 (CRFILT)
HUB_DIS3: R205.2, U61.6 (USBDM_DN3/PRT_DIS_M3), U61.7 (USBDP_DN3/PRT_DIS_P3)
HUB_DIS4: R206.2, U61.8 (USBDM_DN4/PRT_DIS_M4), U61.9 (USBDP_DN4/PRT_DIS_P4)
HUB_NONREM1: R204.1, U61.22 (SDA/SMBDATA/NON_REM1)
HUB_OCN34: R207.2, U61.19 (OCS_N3), U61.21 (OCS_N4)
HUB_PLLFILT: C207.1, U61.34 (PLLFILT)
HUB_RBIAS: R210.1, U61.35 (RBIAS)
HUB_UP_DN: U60.8 (HSD2-), U61.30 (USBDM_UP)
HUB_UP_DP: U60.9 (HSD2+), U61.31 (USBDP_UP)
HUB_XI: C208.1, R211.1, U61.33 (XTALIN/CLKIN), Y60.1
HUB_XO: C209.1, R211.2, U61.32 (XTALOUT), Y60.3
ID_SC: J1.35 (ID_SC), J80.28
ID_SD: J1.36 (ID_SD), J80.27
ILIM: C19.1, R13.1, U10.11 (ILIM)
IP_1V8: C87.1, U50.21 (V1P8)
IP_3V3: C85.1, C86.1, R74.1, R75.1, R76.1, U50.20 (V3P3), U50.44 (DV3P3)
IP_5V: C84.1, U50.19 (V5), U50.22 (VPP)
IP_LEDCLK: R77.1, U50.37 (LED_CLK)
IP_LEDDAT: R78.1, U50.38 (LED_DAT)
IP_RSTN: C88.1, R74.2, U50.45 (RstN)
IP_SCL: R75.2, U50.39 (SCL/EE_CLK)
IP_SDA: R76.2, U50.41 (SDAI/EE_DAT)
LAN0_1V2: C110.1, C111.1, C112.1, C113.1, C114.1, C115.1, L40.2, U40.15 (VDD12_SW_FB), U40.21 (VDD12CORE), U40.25 (VDD12A), U40.30 (VDD12A), U40.42 (VDD12CORE), U40.44 (VDD12A)
LAN0_2V5: C105.1, C106.1, C107.1, C108.1, C109.1, U40.3 (VDD25A), U40.6 (VDD25A), U40.9 (VDD25A), U40.12 (VDD25A), U40.45 (VDD25_REG_OUT)
LAN0_DM: J2.36 (USB3-0-DM), U40.27 (USB2_DM)
LAN0_DP: J2.34 (USB3-0-DP), U40.26 (USB2_DP)
LAN0_EEDI: R102.1, U40.17 (EEDI/GPIO1)
LAN0_FILT: C117.1, U40.48 (REF_FILT)
LAN0_LEDG_K: R104.2, U40.18 (EEDO/LED0/GPIO2)
LAN0_LEDG_K2: D40.1 (K), R104.1
LAN0_LEDY_K: R105.2, U40.19 (EECLK/LED1/GPIO3)
LAN0_LEDY_K2: D41.1 (K), R105.1
LAN0_RBIAS: R101.1, U40.37 (USBRBIAS)
LAN0_REXT: R100.1, U40.47 (REF_REXT)
LAN0_RX_N: J2.40 (USB3-0-TX_N), U40.31 (USB3_RXDP)
LAN0_RX_P: J2.42 (USB3-0-TX_P), U40.32 (USB3_RXDM)
LAN0_SW: L40.1, U40.13 (VDD12_SW_OUT)
LAN0_TR0N: T40.22 (TD1-), U40.2 (TR0N)
LAN0_TR0P: T40.23 (TD1+), U40.1 (TR0P)
LAN0_TR1N: T40.19 (TD2-), U40.5 (TR1N)
LAN0_TR1P: T40.20 (TD2+), U40.4 (TR1P)
LAN0_TR2N: T40.16 (TD3-), U40.8 (TR2N)
LAN0_TR2P: T40.17 (TD3+), U40.7 (TR2P)
LAN0_TR3N: T40.13 (TD4-), U40.11 (TR3N)
LAN0_TR3P: T40.14 (TD4+), U40.10 (TR3P)
LAN0_TX_N: C121.1, U40.29 (USB3_TXDM)
LAN0_TX_P: C120.1, U40.28 (USB3_TXDP)
LAN0_XI: C118.1, U40.40 (XI), Y40.1
LAN0_XO: C119.1, U40.41 (XO), Y40.3
LAN1_1V2: C140.1, C141.1, C142.1, C143.1, C144.1, C145.1, L41.2, U41.15 (VDD12_SW_FB), U41.21 (VDD12CORE), U41.25 (VDD12A), U41.30 (VDD12A), U41.42 (VDD12CORE), U41.44 (VDD12A)
LAN1_2V5: C135.1, C136.1, C137.1, C138.1, C139.1, U41.3 (VDD25A), U41.6 (VDD25A), U41.9 (VDD25A), U41.12 (VDD25A), U41.45 (VDD25_REG_OUT)
LAN1_DM: J2.65 (USB3-1-DM), U41.27 (USB2_DM)
LAN1_DP: J2.63 (USB3-1-DP), U41.26 (USB2_DP)
LAN1_EEDI: R132.1, U41.17 (EEDI/GPIO1)
LAN1_FILT: C147.1, U41.48 (REF_FILT)
LAN1_LEDG_K: R134.2, U41.18 (EEDO/LED0/GPIO2)
LAN1_LEDG_K2: D42.1 (K), R134.1
LAN1_LEDY_K: R135.2, U41.19 (EECLK/LED1/GPIO3)
LAN1_LEDY_K2: D43.1 (K), R135.1
LAN1_RBIAS: R131.1, U41.37 (USBRBIAS)
LAN1_REXT: R130.1, U41.47 (REF_REXT)
LAN1_RX_N: J2.69 (USB3-1-TX_N), U41.32 (USB3_RXDM)
LAN1_RX_P: J2.71 (USB3-1-TX_P), U41.31 (USB3_RXDP)
LAN1_SW: L41.1, U41.13 (VDD12_SW_OUT)
LAN1_TR0N: T41.22 (TD1-), U41.2 (TR0N)
LAN1_TR0P: T41.23 (TD1+), U41.1 (TR0P)
LAN1_TR1N: T41.19 (TD2-), U41.5 (TR1N)
LAN1_TR1P: T41.20 (TD2+), U41.4 (TR1P)
LAN1_TR2N: T41.16 (TD3-), U41.8 (TR2N)
LAN1_TR2P: T41.17 (TD3+), U41.7 (TR2P)
LAN1_TR3N: T41.13 (TD4-), U41.11 (TR3N)
LAN1_TR3P: T41.14 (TD4+), U41.10 (TR3P)
LAN1_TX_N: C151.1, U41.29 (USB3_TXDM)
LAN1_TX_P: C150.1, U41.28 (USB3_TXDP)
LAN1_XI: C148.1, U41.40 (XI), Y41.1
LAN1_XO: C149.1, U41.41 (XO), Y41.3
LED_ACT_K: D51.1 (K), R51.1
LED_PWR_K: D50.1 (K), R50.1
LED_nACT: J1.21 (LED_nACT), R51.2
LED_nPWR: J1.95 (LED_nPWR), R50.2
LO: Q11.4 (G), U10.13 (LO)
MODE3: R23.2, R24.1, U20.15 (MODE)
PCIE_CLK_N: J2.12 (PCIe_CLK_N), J60.53 (REFCLKn)
PCIE_CLK_P: J2.10 (PCIe_CLK_P), J60.55 (REFCLKp)
PCIE_RX_N: J2.18 (PCIe_RX_N), J60.41 (PERn0/SATA-B+)
PCIE_RX_P: J2.16 (PCIe_RX_P), J60.43 (PERp0/SATA-B-)
PCIE_TX_N: J2.24 (PCIe_TX_N), J60.47 (PETn0/SATA-A-)
PCIE_TX_P: J2.22 (PCIe_TX_P), J60.49 (PETp0/SATA-A+)
PCIE_nCLKREQ: J2.2 (PCIe_CLK_nREQ), J60.52 (~CLKREQ)
PCIE_nRST: J2.9 (PCIe_nRST), J60.50 (~PERST)
PCIE_nWAKE: J2.4 (PCIE_nWAKE), J60.54 (~PEWAKE)
PG_3V3: R25.2, U20.9 (PGOOD), U40.35 (RESET_N/PME_CLEAR), U41.35 (RESET_N/PME_CLEAR), U61.26 (RESET_N)
PG_5V: R18.2, U10.10 (PGOOD), U20.12 (EN)
POE0_A_N: J40.2, T40.3 (MX1-)
POE0_A_P: J40.1, T40.2 (MX1+)
POE0_BOB: C90.1, R80.2, R81.2
POE0_B_N: J40.6, T40.6 (MX2-)
POE0_B_P: J40.3, T40.5 (MX2+)
POE0_CT3: R80.1, T40.7 (MCT3)
POE0_CT4: R81.1, T40.10 (MCT4)
POE0_C_N: J40.5, T40.9 (MX3-)
POE0_C_P: J40.4, T40.8 (MX3+)
POE0_D_N: J40.8, T40.12 (MX4-)
POE0_D_P: J40.7, T40.11 (MX4+)
POE0_N: C92.2, D60.2 (A2), T40.1 (MCT1), U50.3 (PortN0)
POE0_P: C92.1, D60.1 (A1), F40.2, T40.4 (MCT2)
POE0_TCT1: C70.1, T40.24 (TCT1)
POE0_TCT2: C71.1, T40.21 (TCT2)
POE0_TCT3: C72.1, T40.18 (TCT3)
POE0_TCT4: C73.1, T40.15 (TCT4)
POE1_A_N: J41.2, T41.3 (MX1-)
POE1_A_P: J41.1, T41.2 (MX1+)
POE1_BOB: C91.1, R82.2, R83.2
POE1_B_N: J41.6, T41.6 (MX2-)
POE1_B_P: J41.3, T41.5 (MX2+)
POE1_CT3: R82.1, T41.7 (MCT3)
POE1_CT4: R83.1, T41.10 (MCT4)
POE1_C_N: J41.5, T41.9 (MX3-)
POE1_C_P: J41.4, T41.8 (MX3+)
POE1_D_N: J41.8, T41.12 (MX4-)
POE1_D_P: J41.7, T41.11 (MX4+)
POE1_N: C93.2, D61.2 (A2), T41.1 (MCT1), U50.5 (PortN1)
POE1_P: C93.1, D61.1 (A1), F41.2, T41.4 (MCT2)
POE1_TCT1: C74.1, T41.24 (TCT1)
POE1_TCT2: C75.1, T41.21 (TCT2)
POE1_TCT3: C76.1, T41.18 (TCT3)
POE1_TCT4: C77.1, T41.15 (TCT4)
PWR_BUT: J1.92 (PWR_Button), SW50.1
RT: R12.1, U10.2 (RT)
SS: C18.1, U10.3 (SS/TRK)
SW: C21.2, L10.1, Q10.1 (S), Q10.2 (S), Q10.3 (S), Q11.5 (D), R13.2, U10.19 (SW)
SW3: C49.2, L20.1, U20.6 (SW), U20.19 (SW), U20.20 (SW)
USBA0_DN: D71.3 (I/O2), D71.4 (I/O2), J51.2 (D-), U61.1 (USBDM_DN1/PRT_DIS_M1)
USBA0_DP: D71.1 (I/O1), D71.6 (I/O1), J51.3 (D+), U61.2 (USBDP_DN1/PRT_DIS_P1)
USBA0_EN: U61.12 (PRTPWR1/BC_EN1), U62.4 (EN)
USBA0_OCN: R208.2, U61.13 (OCS_N1), U62.3 (~FLG)
USBA0_VBUS: C211.1, C212.1, D71.5 (VBUS), J51.1 (VBUS), U62.1 (OUT)
USBA1_DN: D72.3 (I/O2), D72.4 (I/O2), J52.2 (D-), U61.3 (USBDM_DN2/PRT_DIS_M2)
USBA1_DP: D72.1 (I/O1), D72.6 (I/O1), J52.3 (D+), U61.4 (USBDP_DN2/PRT_DIS_P2)
USBA1_EN: U61.16 (PRTPWR2/BC_EN2), U63.4 (EN)
USBA1_OCN: R209.2, U61.17 (OCS_N2), U63.3 (~FLG)
USBA1_VBUS: C214.1, C215.1, D72.5 (VBUS), J52.1 (VBUS), U63.1 (OUT)
USBC_CC1: J50.A5 (CC1), R200.1
USBC_CC2: J50.B5 (CC2), R201.1
USBC_DN: D70.3 (I/O2), D70.4 (I/O2), J50.A7 (D-), J50.B7 (D-), U60.6 (HSD1-)
USBC_DP: D70.1 (I/O1), D70.6 (I/O1), J50.A6 (D+), J50.B6 (D+), U60.7 (HSD1+)
USBC_VBUS: D70.5 (VBUS), J50.A4 (VBUS), J50.A9 (VBUS), J50.B4 (VBUS), J50.B9 (VBUS)
USB_OTG_ID: J2.1 (USB_OTG_ID), SW51.3 (C)
VBAT: BT50.1 (+), J1.76 (VBAT)
VCC: C20.1, U10.14 (VCC)
VCC3: C48.1, R23.1, U20.17 (VCC)
VIN_RAW: F1.1, J20.1
nRPIBOOT: J1.93 (nRPIBOOT), SW51.1 (A), U60.2 (SEL)

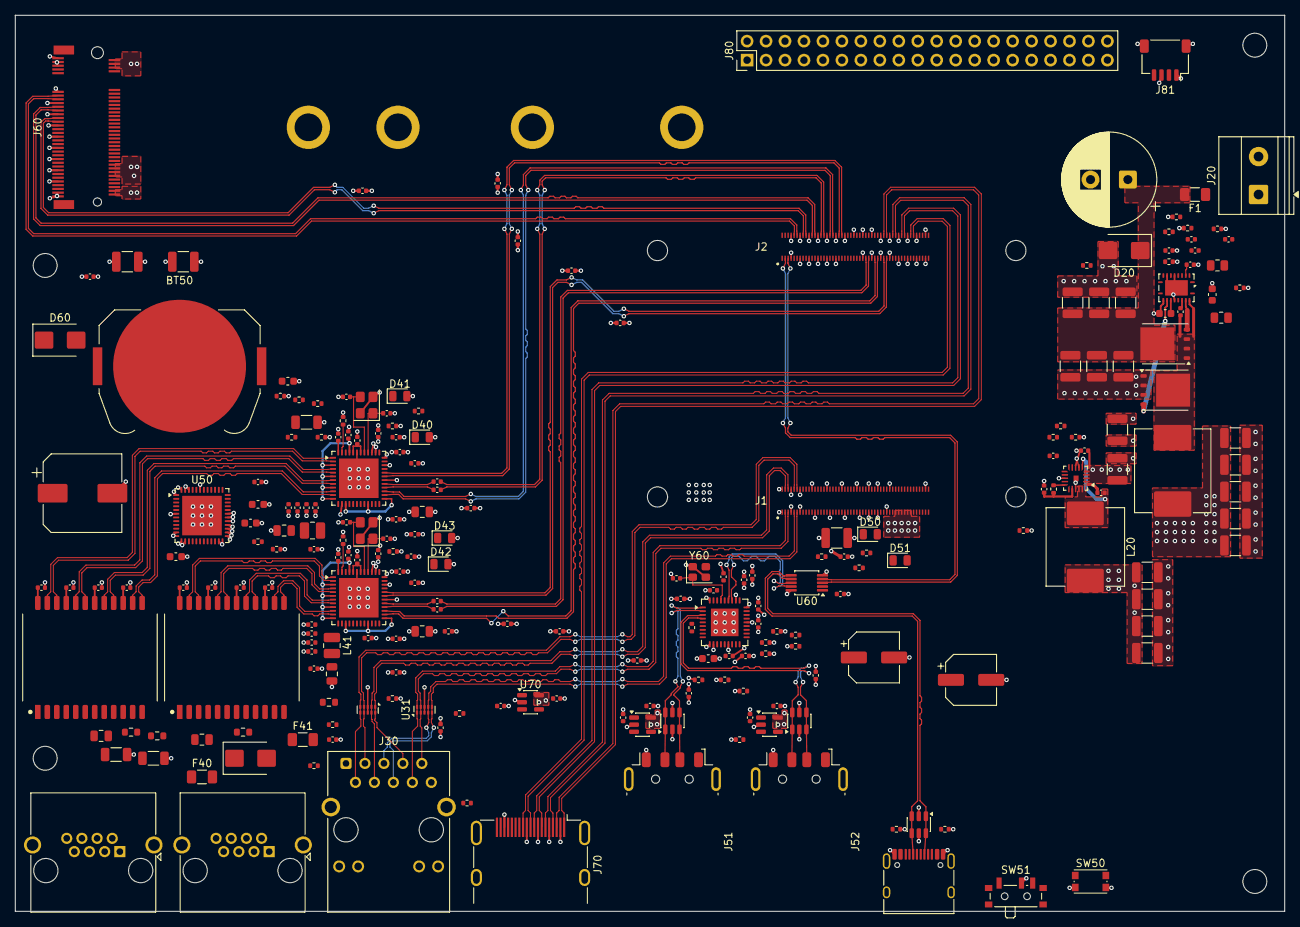
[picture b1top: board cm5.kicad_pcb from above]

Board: 4 copper layers, 170.0 x 120.0 mm, 241 parts (0 on the bottom side), 230 nets.

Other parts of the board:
H1, H2, H3, H4: MountingHole_3.2mm_M3
H5, H6, H7, H8: MountingHole_2.7mm_M2.5

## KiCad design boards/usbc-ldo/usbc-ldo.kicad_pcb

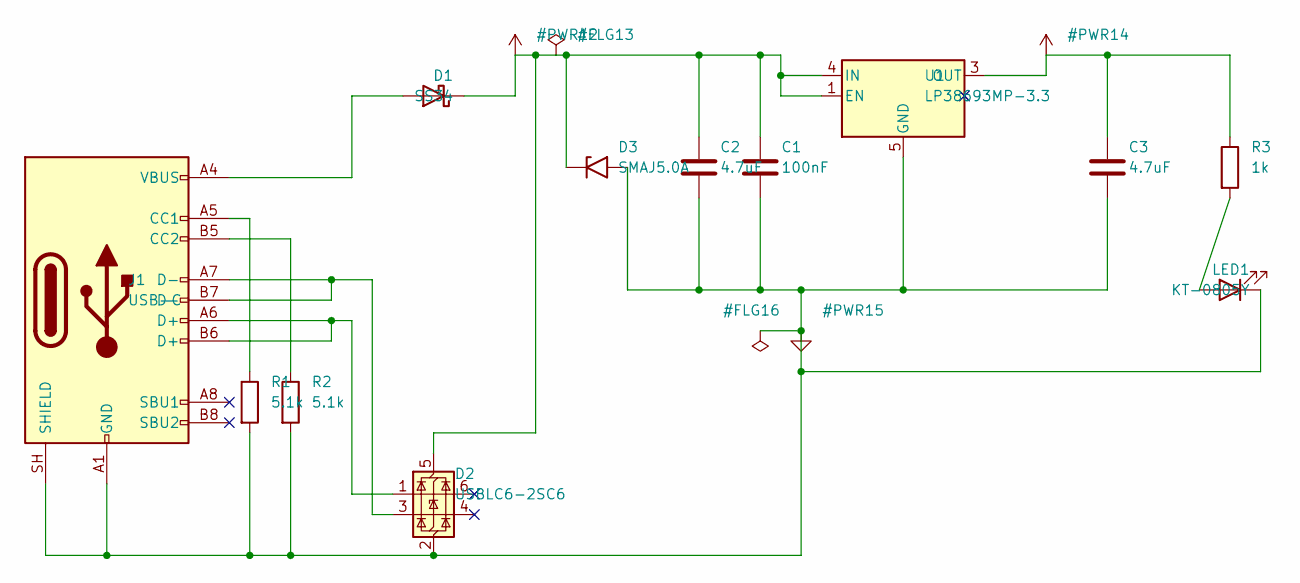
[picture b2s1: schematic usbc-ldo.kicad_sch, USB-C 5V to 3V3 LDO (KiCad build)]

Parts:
C1: 100nF; C_0402_1005Metric
C2, C3: 4.7uF; C_0805_2012Metric
D1: SS34; D_SMA
D2: USBLC6-2SC6; SOT-23-6
D3: SMAJ5.0A; D_SMA
J1: USB-C; USB_C_Receptacle_HRO_TYPE-C-31-M-12
LED1: KT-0805Y; LED_0805_2012Metric
R1, R2: 5.1k; R_0402_1005Metric
R3: 1k; R_0402_1005Metric
U1: LP38693MP-3.3; SOT-223-5

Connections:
+3V3: C3.1, R3.1, U1.3 (OUT)
+5V: C1.1, C2.1, D1.1 (K), D2.5 (VBUS), D3.1 (A1), U1.1 (EN), U1.4 (IN)
GND: C1.2, C2.2, C3.2, D2.2 (GND), D3.2 (A2), J1.A1 (GND), J1.A12 (GND), J1.B1 (GND), J1.B12 (GND), J1.SH (SHIELD), LED1.1 (K), R1.2, R2.2, U1.5 (GND)
unnamed: D1.2 (A), J1.A4 (VBUS), J1.A9 (VBUS), J1.B4 (VBUS), J1.B9 (VBUS)
unnamed: D2.1 (I/O1), J1.A6 (D+), J1.B6 (D+)
unnamed: D2.3 (I/O2), J1.A7 (D-), J1.B7 (D-)
unnamed: J1.A5 (CC1), R1.1
unnamed: J1.B5 (CC2), R2.1
unnamed: LED1.2 (A), R3.2

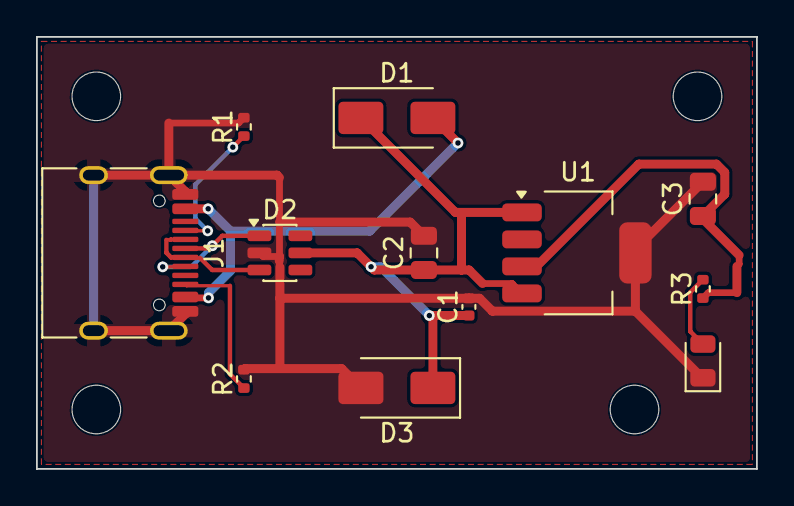
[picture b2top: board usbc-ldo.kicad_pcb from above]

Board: 2 copper layers, 40.0 x 24.0 mm, 16 parts (0 on the bottom side), 9 nets.

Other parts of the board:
H1, H2, H3, H4: MountingHole_2.7mm_M2.5

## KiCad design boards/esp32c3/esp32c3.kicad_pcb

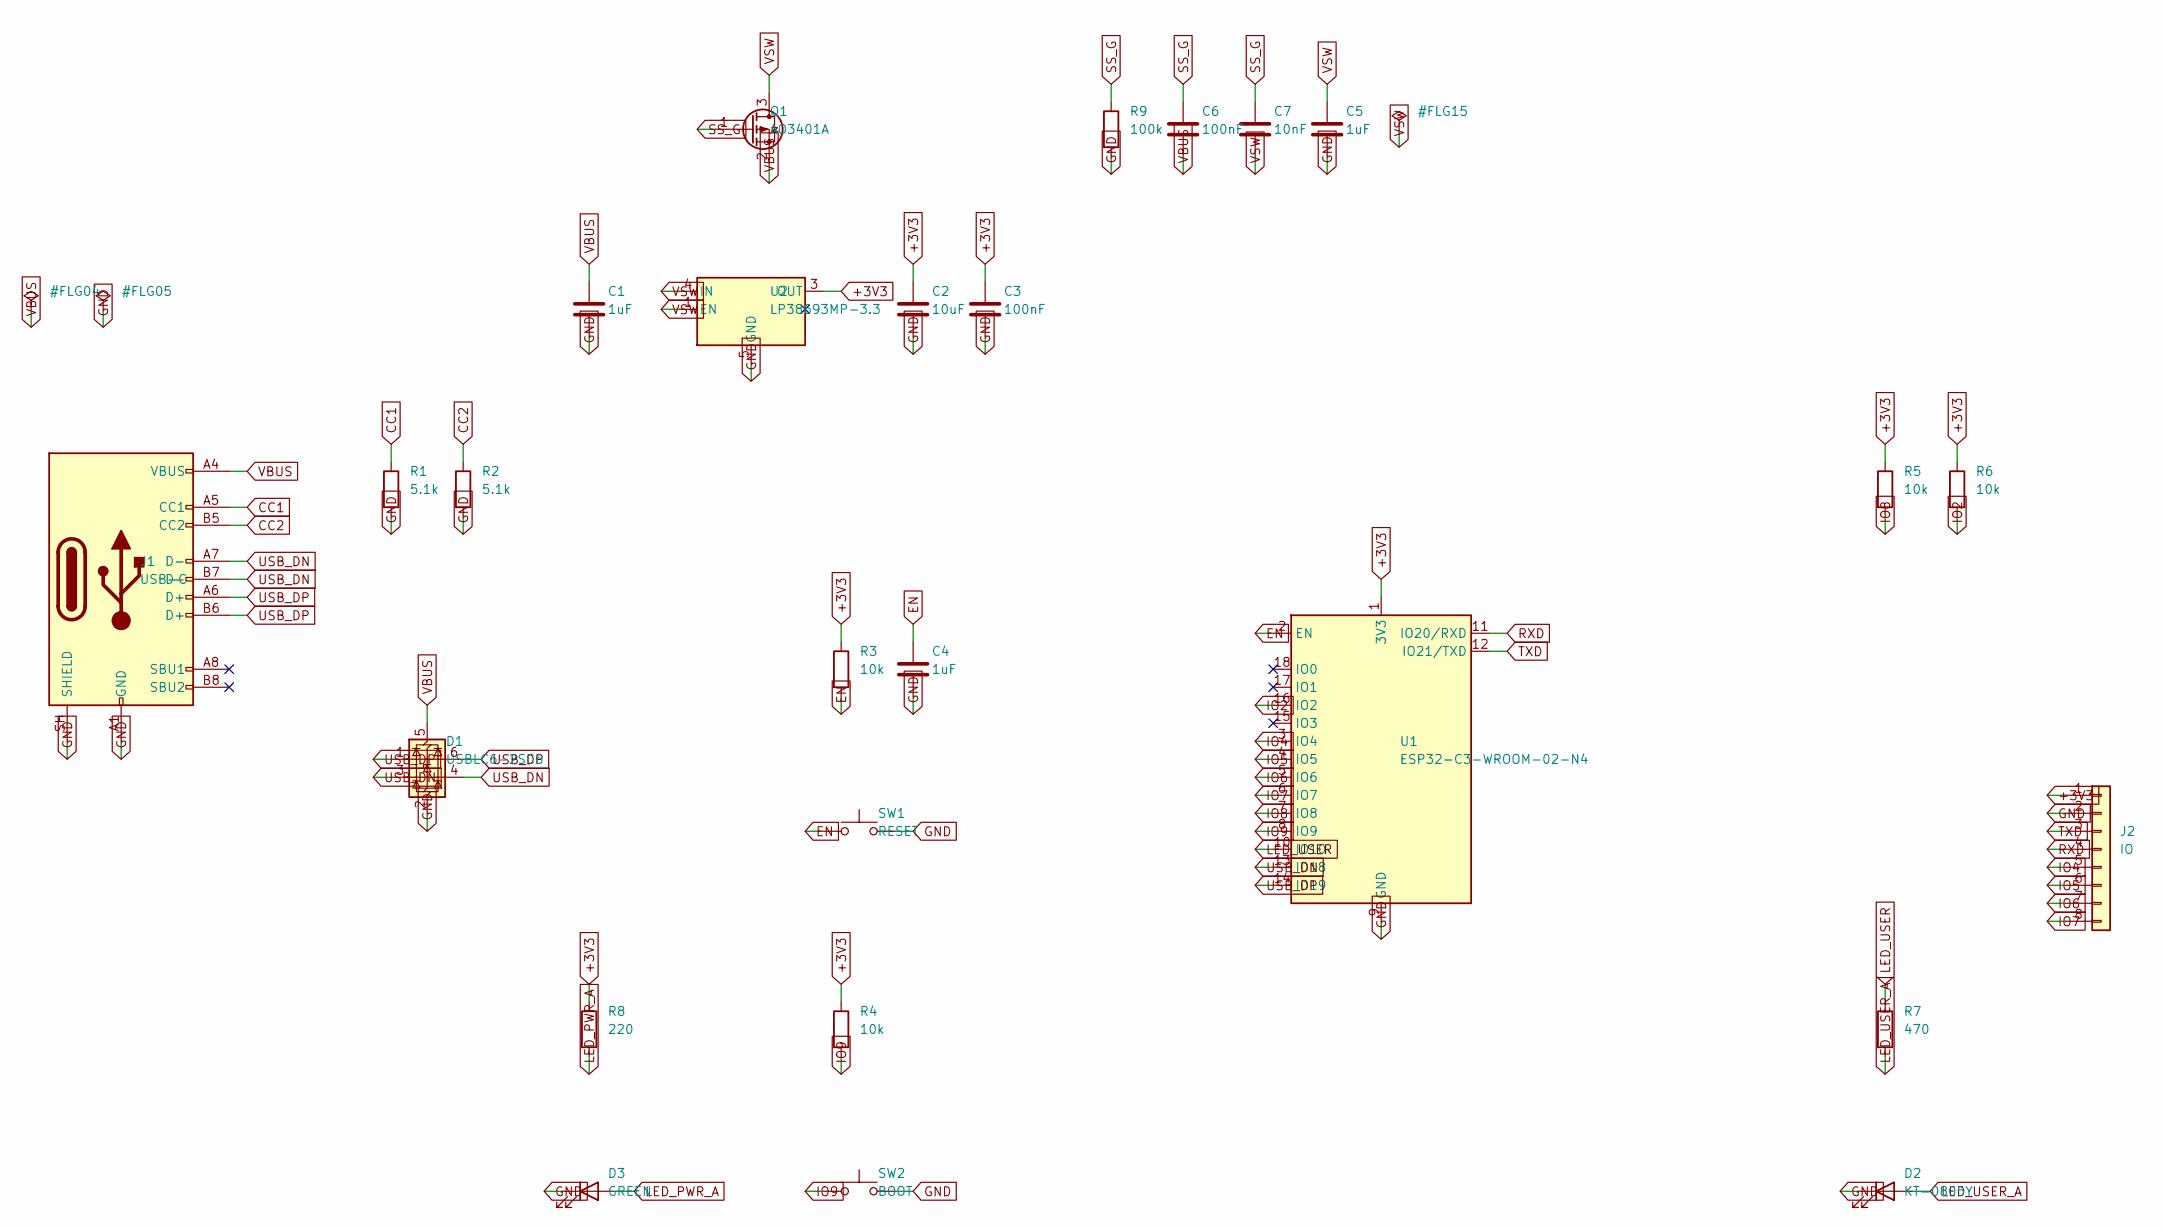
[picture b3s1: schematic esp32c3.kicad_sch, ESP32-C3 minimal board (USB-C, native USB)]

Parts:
C1, C4, C5: 1uF; C_0402_1005Metric
C2: 10uF; C_0805_2012Metric
C3, C6: 100nF; C_0402_1005Metric
C7: 10nF; C_0402_1005Metric
D1: USBLC6-2SC6; SOT-23-6
D2: KT-0805Y; LED_0805_2012Metric
D3: GREEN; LED_0805_2012Metric
J1: USB-C; USB_C_Receptacle_HRO_TYPE-C-31-M-12
J2: IO; PinHeader_1x08_P2.54mm_Vertical
Q1: AO3401A; SOT-23
R1, R2: 5.1k; R_0402_1005Metric
R3, R4, R5, R6: 10k; R_0402_1005Metric
R7: 470; R_0402_1005Metric
R8: 220; R_0402_1005Metric
R9: 100k; R_0402_1005Metric
SW1: RESET; SW_Push_1P1T_NO_CK_KMR2
SW2: BOOT; SW_Push_1P1T_NO_CK_KMR2
U1: ESP32-C3-WROOM-02-N4; ESP32-C3-WROOM-02
U2: LP38693MP-3.3; SOT-223-5

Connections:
+3V3: C2.1, C3.1, J2.1, R3.1, R4.1, R5.1, R6.1, R8.1, U1.1 (3V3), U2.3 (OUT)
CC1: J1.A5 (CC1), R1.1
CC2: J1.B5 (CC2), R2.1
EN: C4.1, R3.2, SW1.1, U1.2 (EN)
GND: C1.2, C2.2, C3.2, C4.2, C5.2, D1.2 (GND), D2.1 (K), D3.1 (K), J1.A1 (GND), J1.A12 (GND), J1.B1 (GND), J1.B12 (GND), J1.SH (SHIELD), J2.2, R1.2, R2.2, R9.2, SW1.2, SW2.2, U1.9 (GND), U1.19 (GND), U2.5 (GND)
IO2: R6.2, U1.16 (IO2)
IO4: J2.5, U1.3 (IO4)
IO5: J2.6, U1.4 (IO5)
IO6: J2.7, U1.5 (IO6)
IO7: J2.8, U1.6 (IO7)
IO8: R5.2, U1.7 (IO8)
IO9: R4.2, SW2.1, U1.8 (IO9)
LED_PWR_A: D3.2 (A), R8.2
LED_USER: R7.1, U1.10 (IO10)
LED_USER_A: D2.2 (A), R7.2
RXD: J2.4, U1.11 (IO20/RXD)
SS_G: C6.1, C7.1, Q1.1 (G), R9.1
TXD: J2.3, U1.12 (IO21/TXD)
USB_DN: D1.3 (I/O2), D1.4 (I/O2), J1.A7 (D-), J1.B7 (D-), U1.13 (IO18)
USB_DP: D1.1 (I/O1), D1.6 (I/O1), J1.A6 (D+), J1.B6 (D+), U1.14 (IO19)
VBUS: C1.1, C6.2, D1.5 (VBUS), J1.A4 (VBUS), J1.A9 (VBUS), J1.B4 (VBUS), J1.B9 (VBUS), Q1.2 (S)
VSW: C5.1, C7.2, Q1.3 (D), U2.1 (EN), U2.4 (IN)

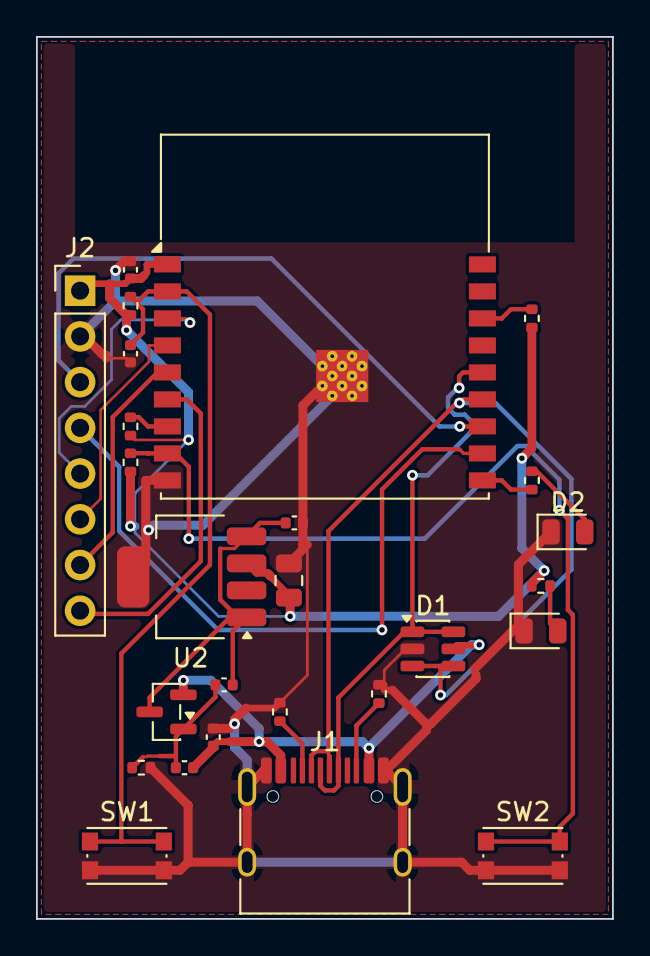
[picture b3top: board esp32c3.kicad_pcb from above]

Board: 2 copper layers, 32.0 x 49.0 mm, 26 parts (0 on the bottom side), 22 nets.

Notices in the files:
boards/cm5/README.md:
焊盤 0.2 × 0.7 mm、腳距 0.4 mm、每顆 2 排 × 50。官方檔只寫 `Copyright © 2024 Raspberry Pi Ltd.`、
